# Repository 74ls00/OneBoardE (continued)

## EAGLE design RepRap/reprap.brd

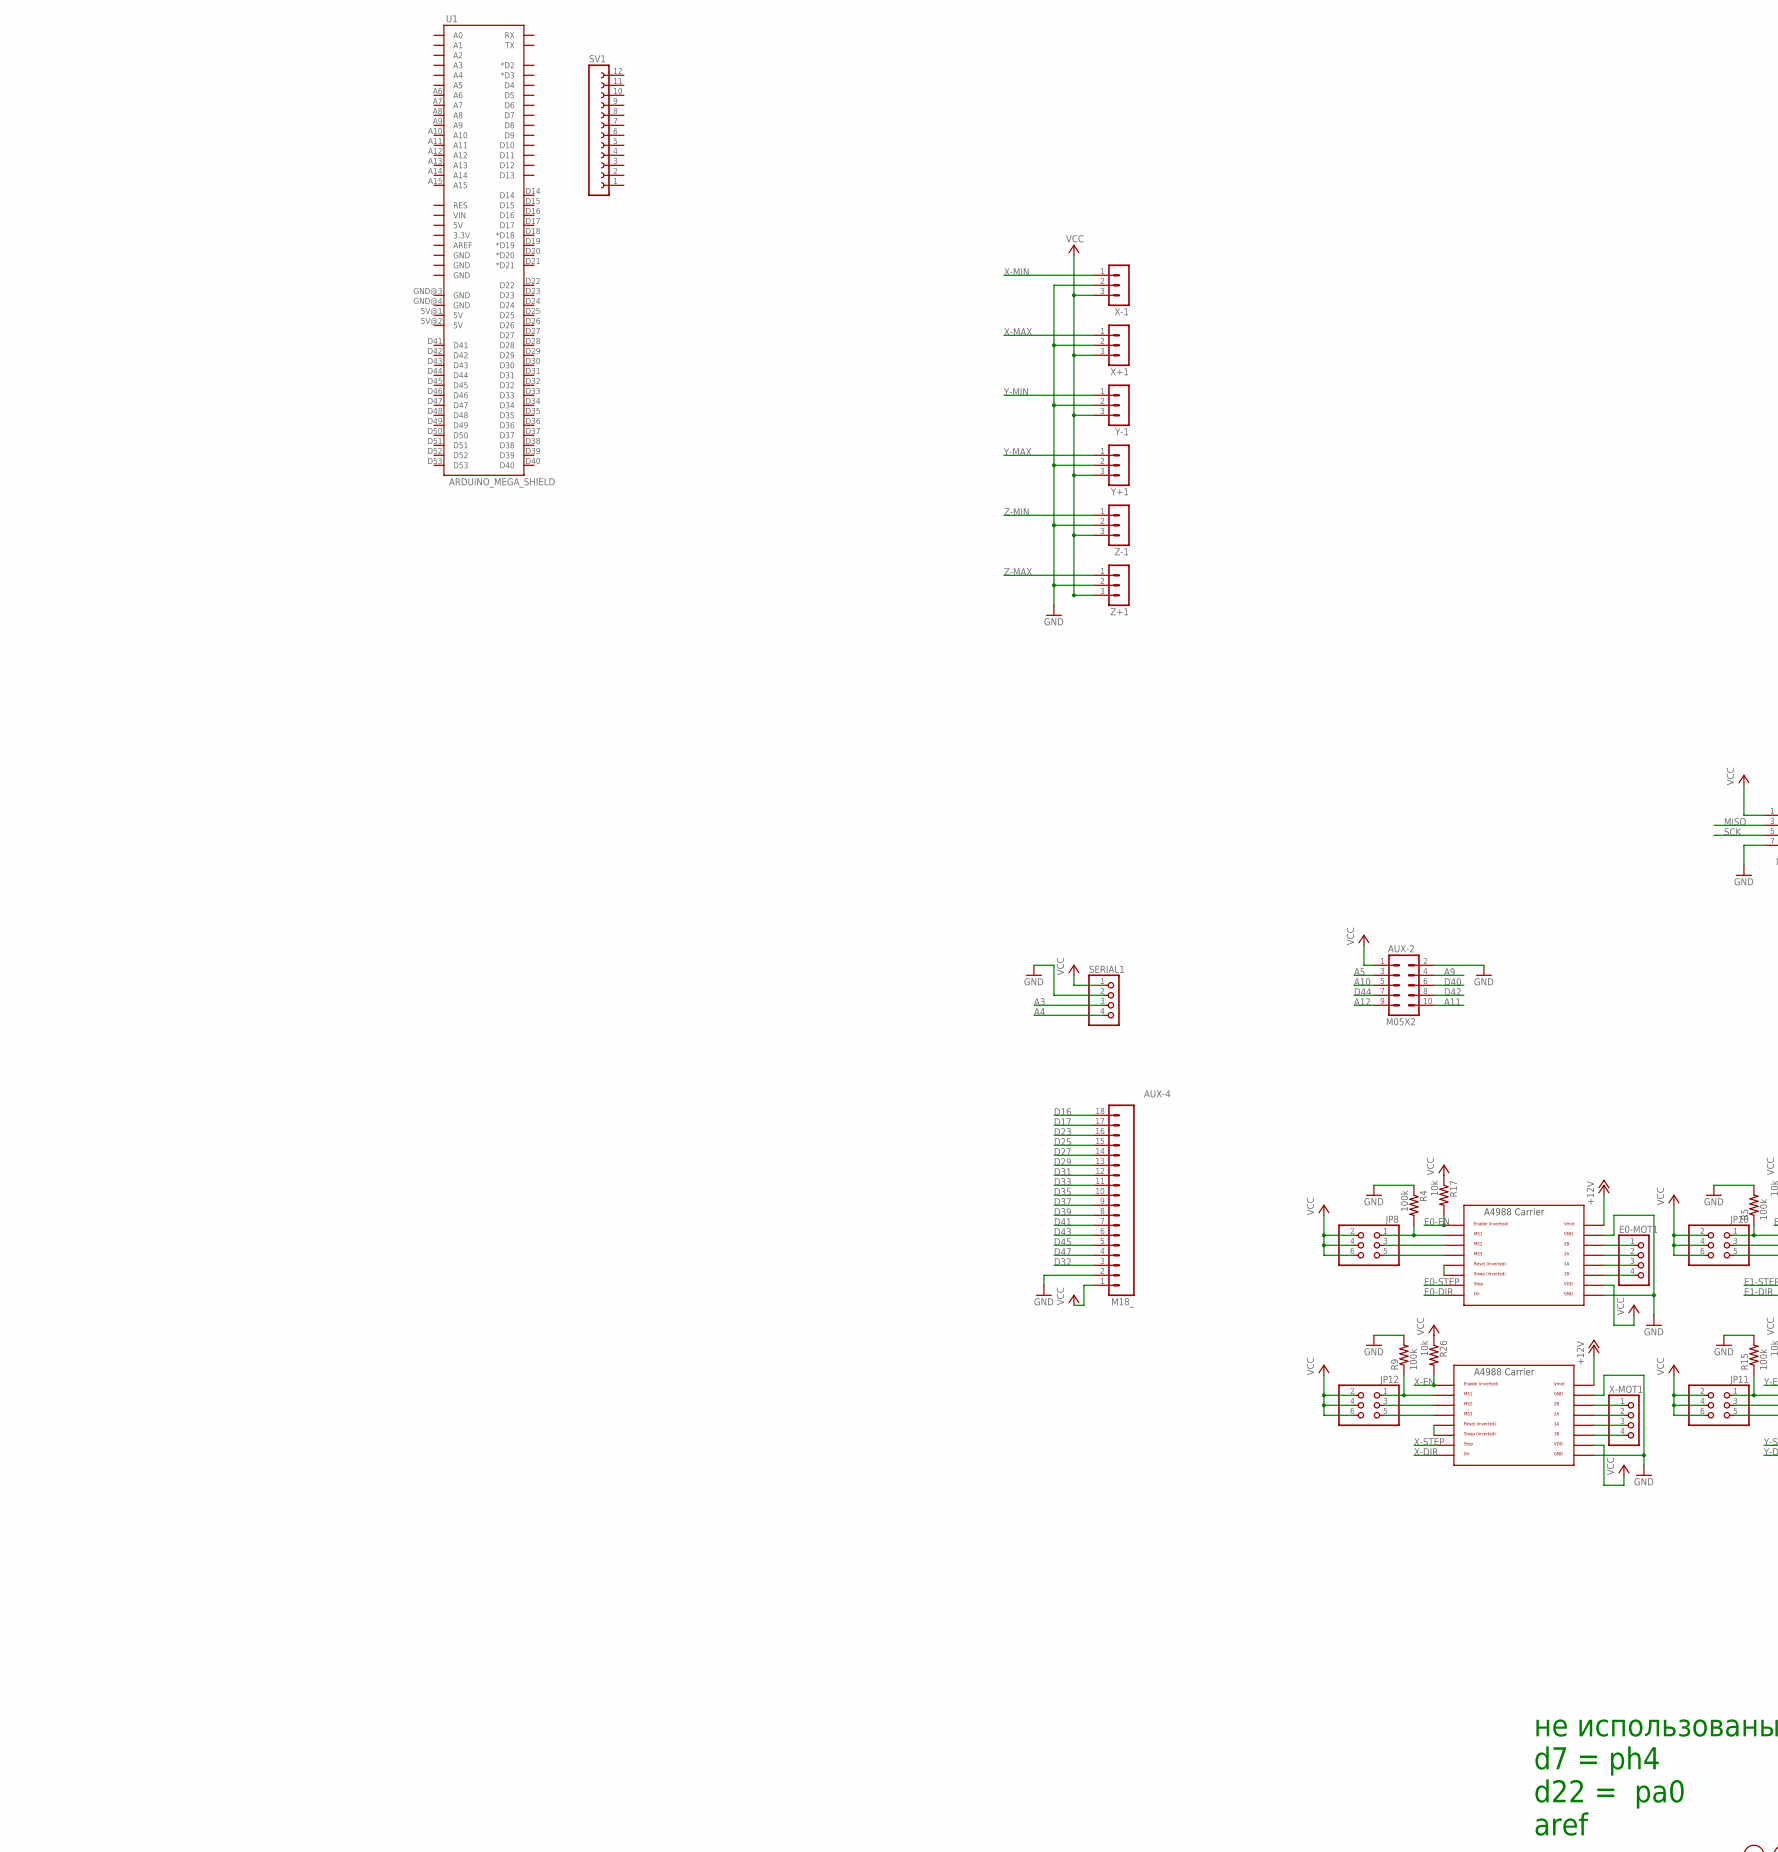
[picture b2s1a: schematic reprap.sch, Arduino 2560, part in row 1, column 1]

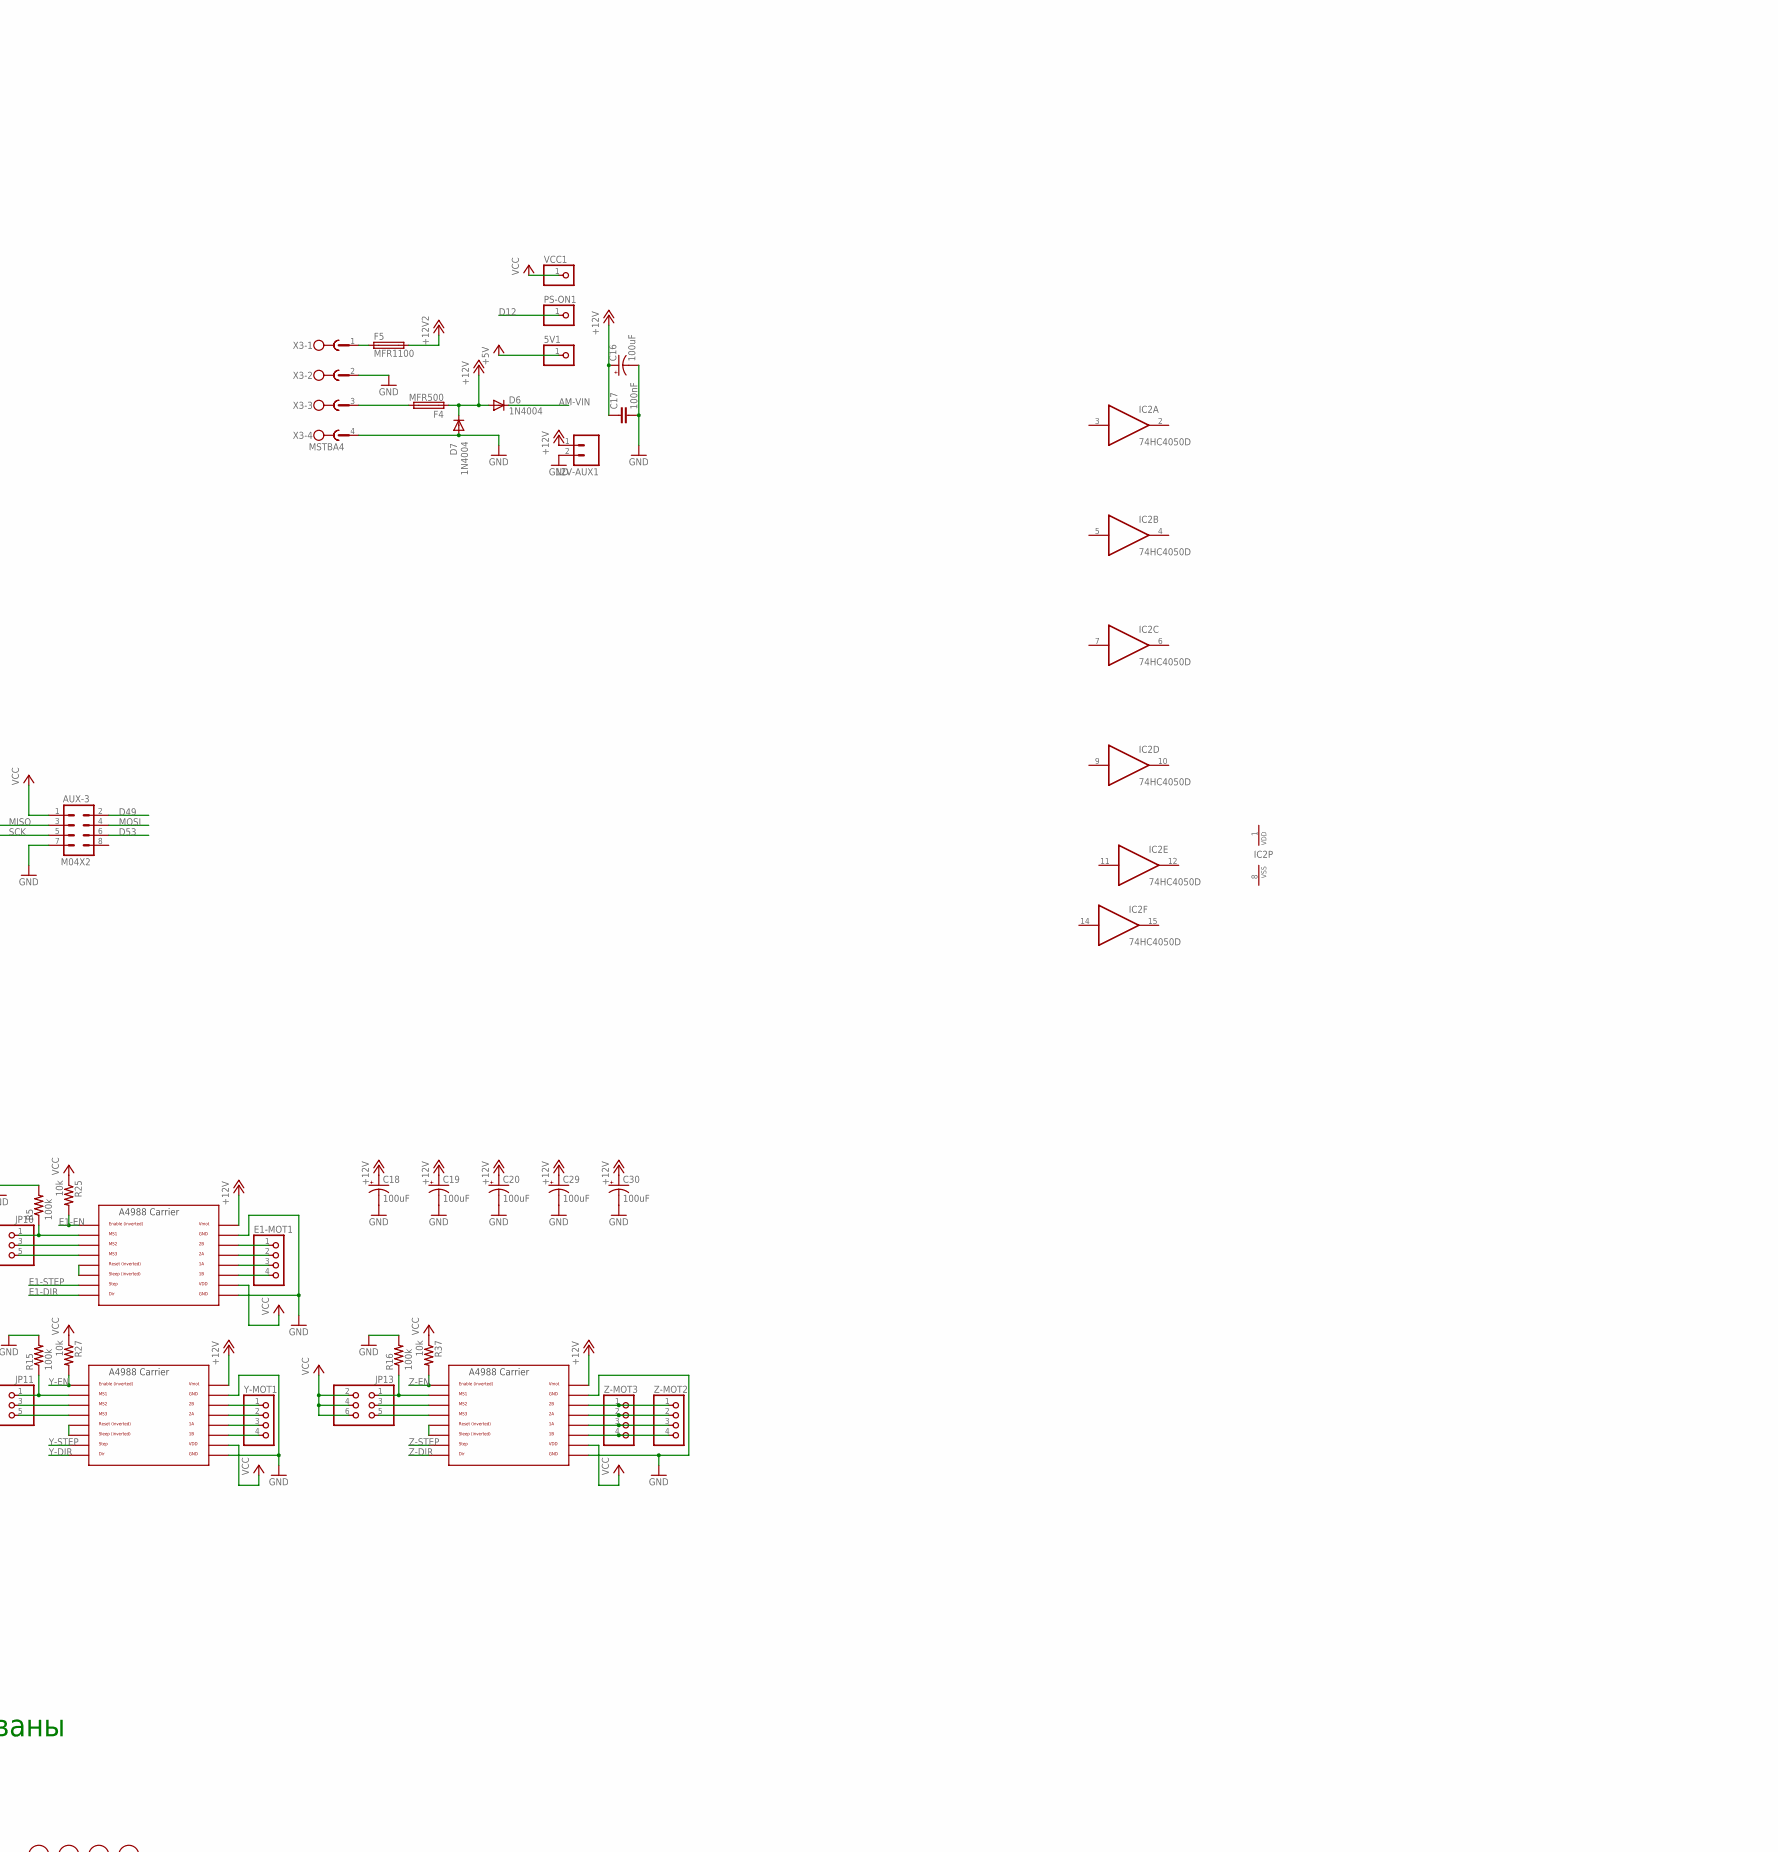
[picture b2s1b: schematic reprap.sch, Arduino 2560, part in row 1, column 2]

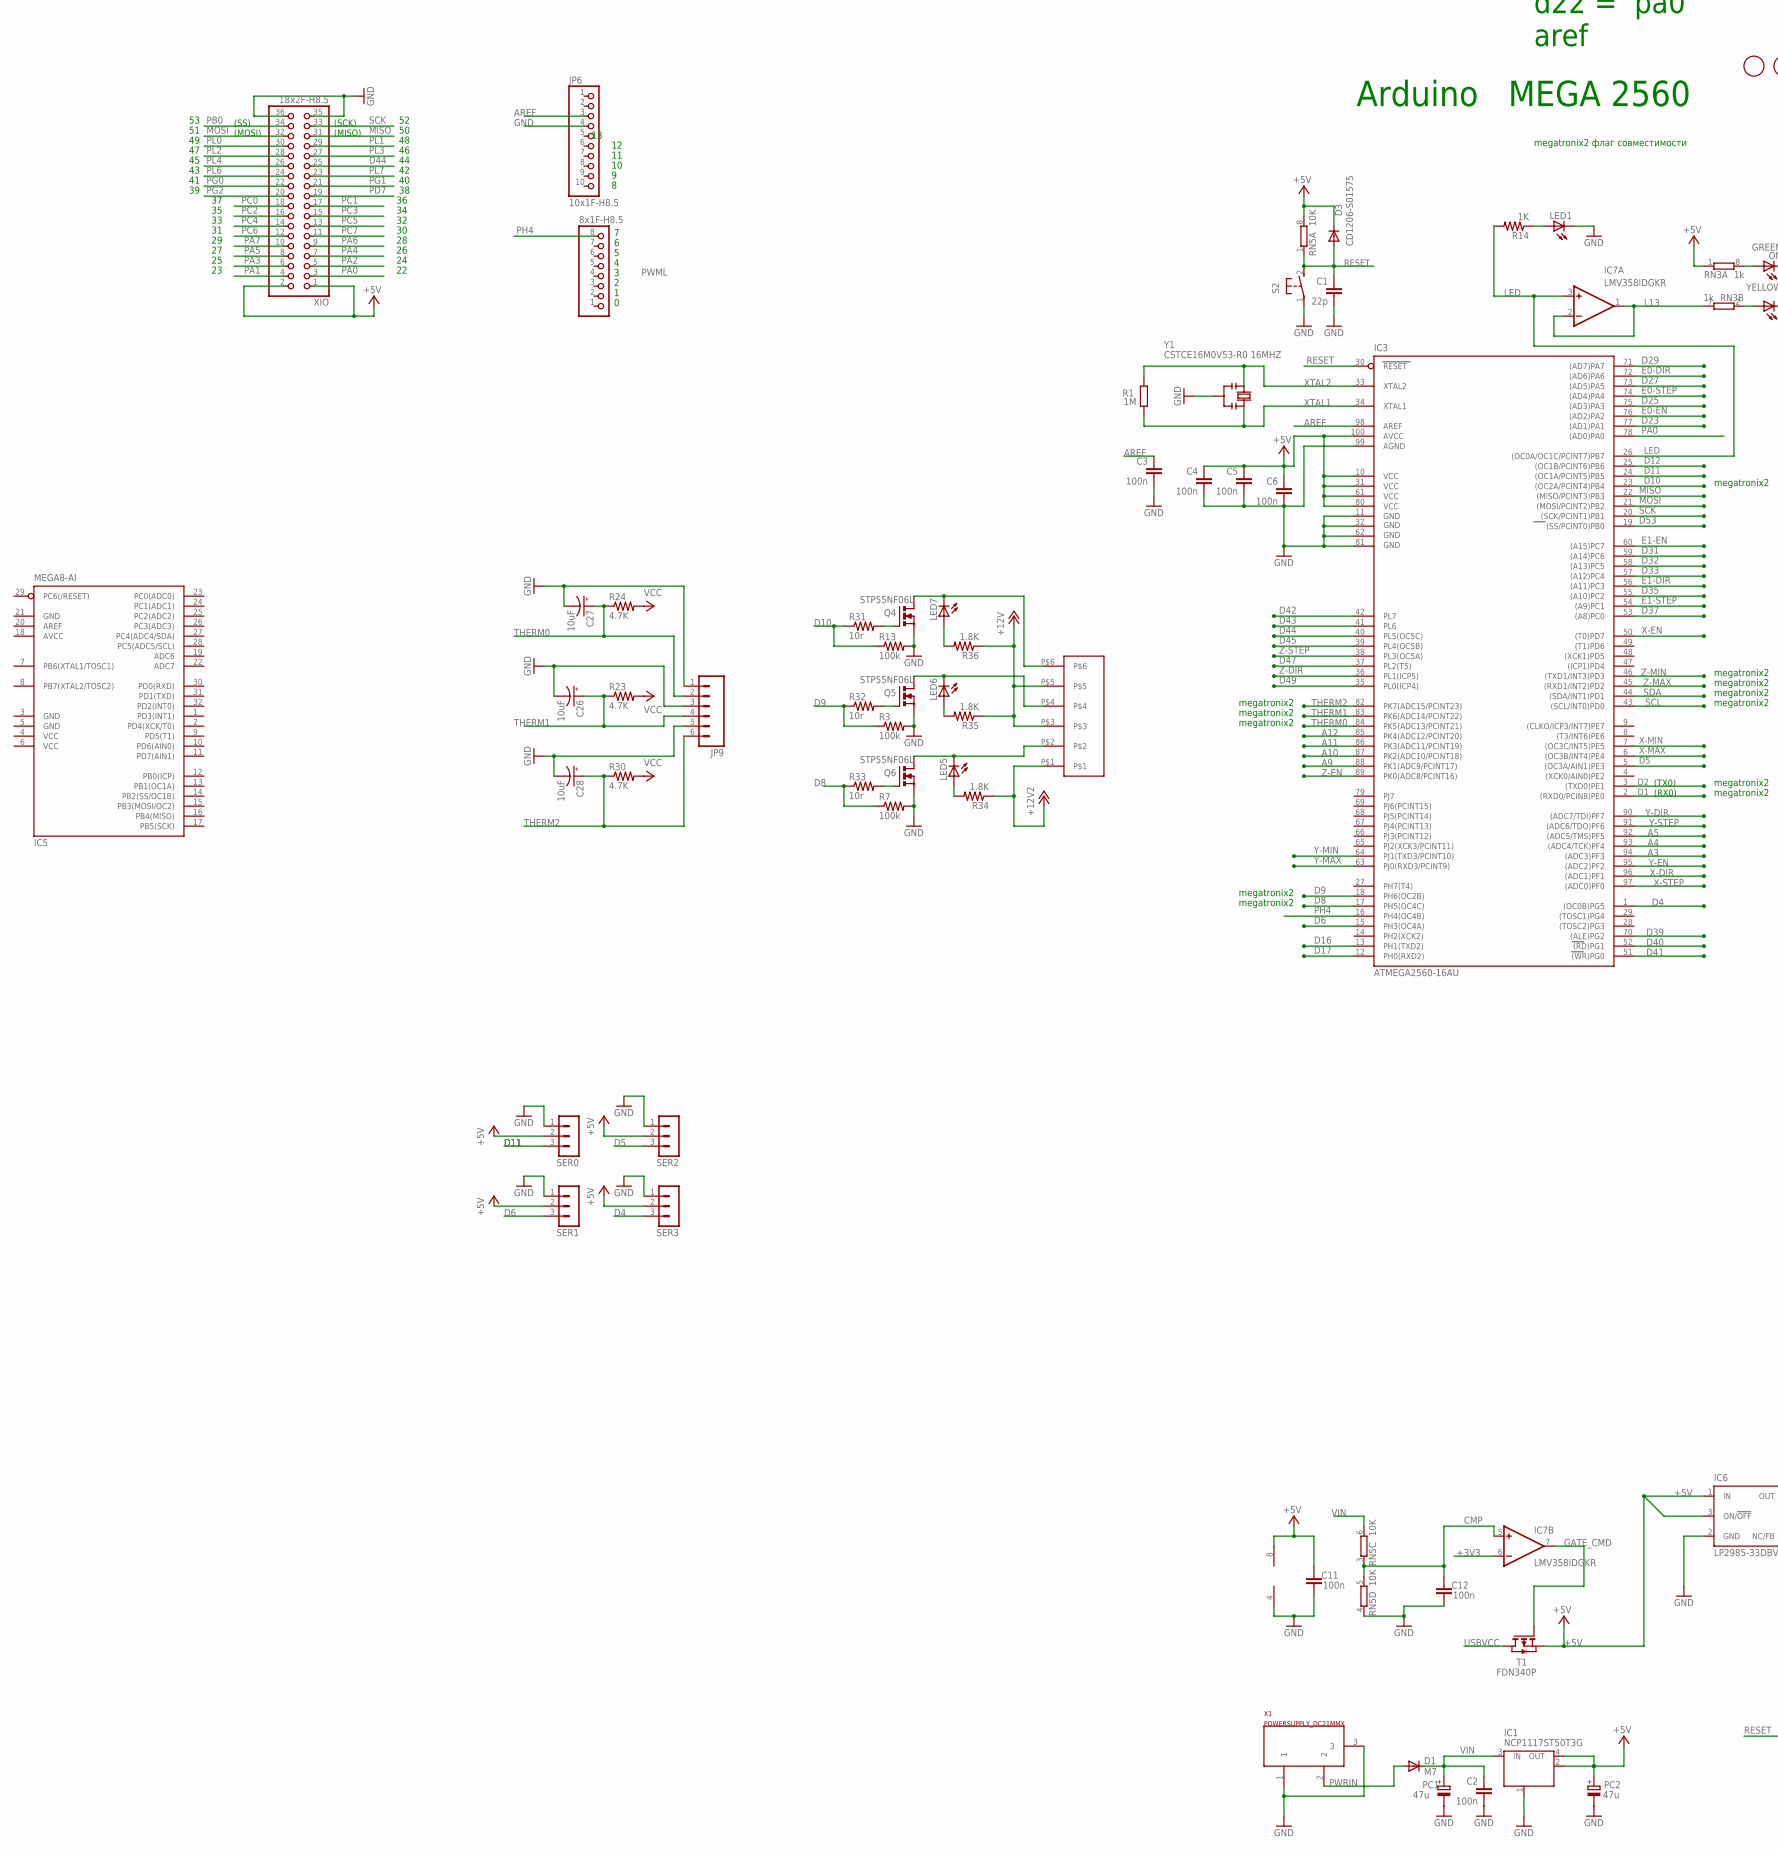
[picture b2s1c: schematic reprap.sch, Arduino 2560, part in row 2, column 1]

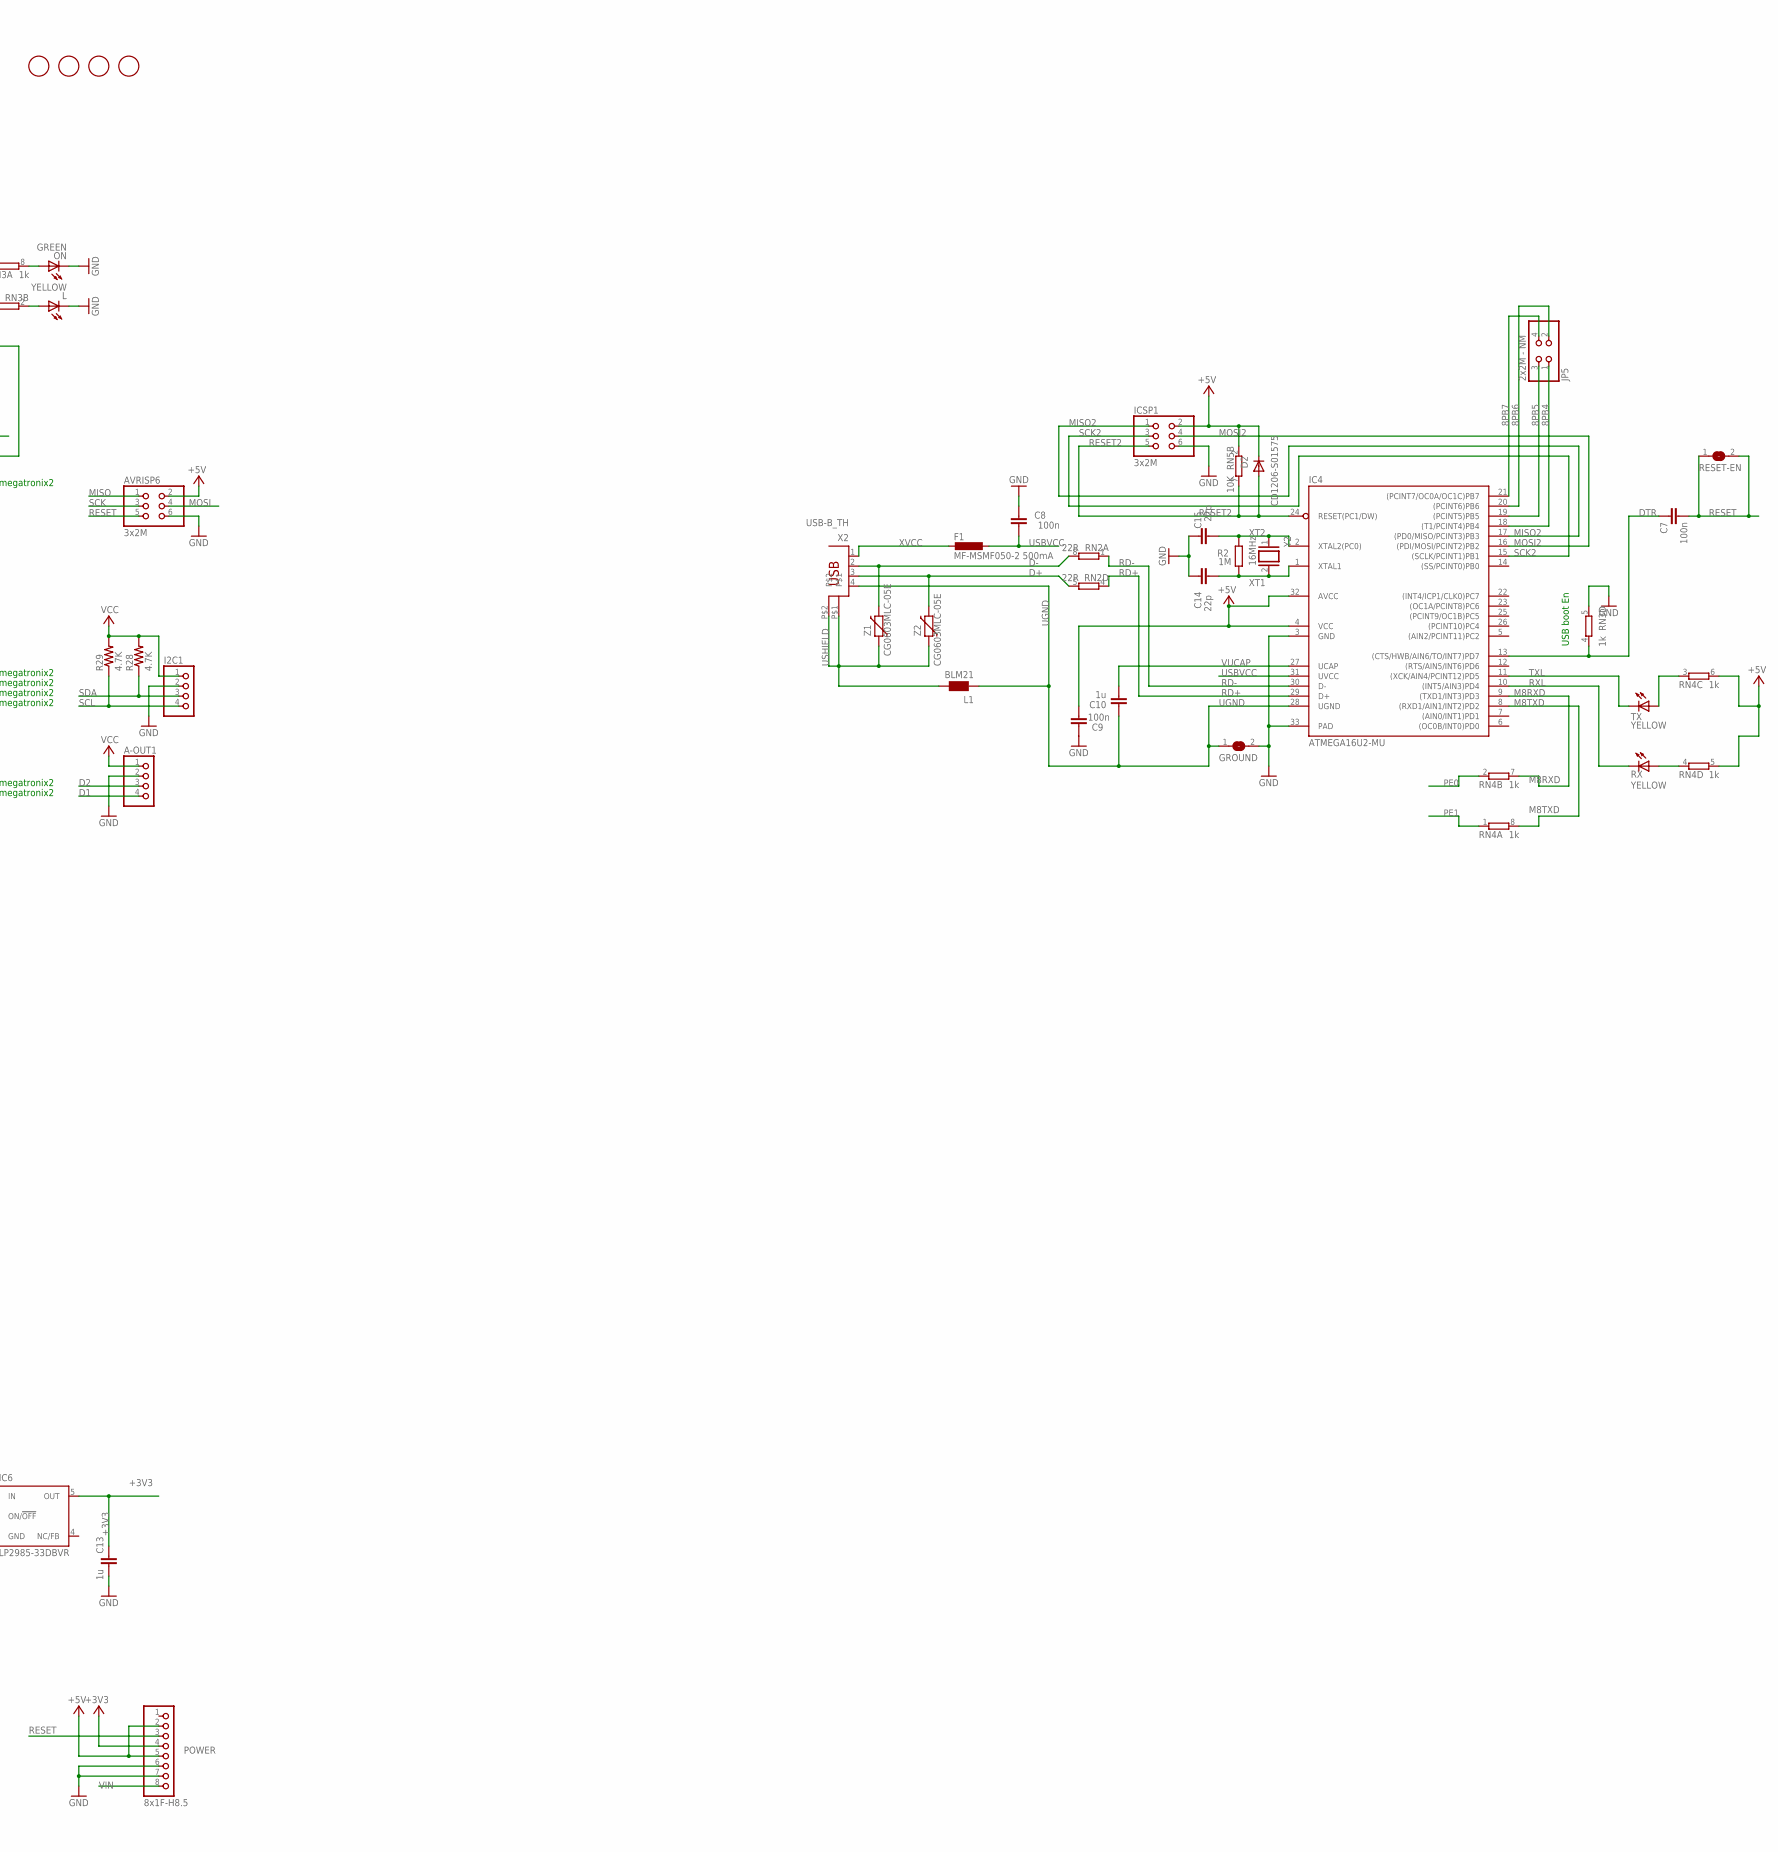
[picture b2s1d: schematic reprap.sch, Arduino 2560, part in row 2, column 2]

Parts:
5V1: PINHD-1X1; 1X01
12V-AUX1: M02PTH; 1X02
A-OUT1: PINHD-1X4; 1X04
AUX-2: M05X2; 2X5
AUX-3: M04X2; 2X4
AUX-4: M18_; 1X18
AVRISP6: 3x2M; 2X03
C1, C14, C15: 22p; C0603-ROUND
C2, C3, C4, C5, C6, C7, C8, C9, C11, C12: 100n; C0603-ROUND
C10, C13: 1u; C0603-ROUND
C16, C18, C19, C20, C29, C30: 100uF; 153CLV-0605
C17: 100nF; C0805
C26, C27, C28: 10uF; 153CLV-0405
D1: M7; SMB
D2, D3: CD1206-S01575; MINIMELF
D6, D7: 1N4004; DO41-10
E0-MOT1, E1-MOT1: PINHD-1X4; 1X04
F1: MF-MSMF050-2 500mA; L1812
F4: MFR500
F5: MFR1100
FD1, FD2, FD3, FD4: FIDUCIALMOUNT; FIDUCIA-MOUNT
GROUND: SJ
I2C1: PINHD-1X4; 1X04
IC1: NCP1117ST50T3G; SOT223
IC2: 74HC4050D; SO16
IC3: ATMEGA2560-16AU; TQFP100
IC4: ATMEGA16U2-MU; MLF32
IC5: MEGA8-AI; TQFP32-08
IC6: LP2985-33DBVR; SOT23-DBV
IC7: LMV358IDGKR; MSOP08
ICSP1: 3x2M; 2X03
JP5: 2x2M - NM; 2X02
JP6: 10x1F-H8.5; 1X10
JP8, JP10, JP11, JP12, JP13: PINHD-2X3; 2X03
JP9: M06SIP; 1X06
L: YELLOW; CHIP-LED0805
L1: BLM21; 0805
LED1, LED5, LED6, LED7: LEDCHIP-LED0805; CHIP-LED0805
ON: GREEN; CHIP-LED0805
PC1, PC2: 47u; PANASONIC_D
POWER: 8x1F-H8.5; 1X08
PS-ON1: PINHD-1X1; 1X01
PWML: 8x1F-H8.5; 1X08
Q4, Q5, Q6: STP55NF06L; TO220BV
R1, R2: 1M; R0603-ROUND
R3, R4, R5, R7, R9, R13, R15, R16: 100k; R0805
R14: 1K; R0805
R17, R25, R26, R27, R37: 10k; R0805
R23, R24, R28, R29, R30: 4.7K; R0805
R31, R33: 10r; R0805
R32: 10r; M0805
R34, R35, R36: 1.8K; R0805
RESET-EN: SJ
RN2: 22R; CAY16
RN3, RN4: 1k; CAY16
RN5: 10K; CAT16
RX: YELLOW; CHIP-LED0805
S2: 31-XX; B3F-31XX
SER0, SER1, SER2, SER3: 3PIN-HEADER
SERIAL1: PINHD-1X4; 1X04
SV1: FE12-1; FE12
T1: FDN340P; SOT-23
TX: YELLOW; CHIP-LED0805
U1: ARDUINO_MEGA_SHIELD
U$1: 282837-6
U$2, U$3, U$9, U$10, U$11: A4988BREAKOUT
VCC1: PINHD-1X1; 1X01
X1: POWERSUPPLY_DC21MMX; POWERSUPPLY_DC-21MM
X2: USB-B_TH; PN61729
X3: MSTBA4
X+1: 3PIN-HEADER
X-1: 3PIN-HEADER
X-MOT1: PINHD-1X4; 1X04
XIO: 18x2F-H8.5; 2X18
Y1: CSTCE16M0V53-R0 16MHZ; RESONATOR
Y2: 16MHz; QS
Y+1: 3PIN-HEADER
Y-1: 3PIN-HEADER
Y-MOT1: PINHD-1X4; 1X04
Z1, Z2: CG0603MLC-05E; CT/CN0603
Z+1: 3PIN-HEADER
Z-1: 3PIN-HEADER
Z-MOT2, Z-MOT3: PINHD-1X4; 1X04

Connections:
5V: U1.5V@0 (5V)
8PB4: IC4.18 ((T1/PCINT4)PB4), JP5.1
8PB5: IC4.19 ((PCINT5)PB5), JP5.3
8PB6: IC4.20 ((PCINT6)PB6), JP5.2
8PB7: IC4.21 ((PCINT7/OC0A/OC1C)PB7), JP5.4
+3V3: C13.2, IC6.5 (OUT), IC7.6 (-IN), POWER.4
+5V: 5V1.1, AVRISP6.2, C4.1, C5.1, C6.1, C9.1, C11.2, D2.C, D3.C, IC1.2 (OUT), IC1.4 (OUT), IC3.10 (VCC), IC3.31 (VCC1), IC3.61 (VCC2), IC3.80 (VCC3), IC3.100 (AVCC), IC4.4 (VCC), IC4.32 (AVCC), IC6.1 (IN), IC6.3 (ON/!OFF), IC7.8 (V+), ICSP1.2, PC2.+, POWER.2, POWER.5, RN3.1, RN4.5 (2), RN4.6 (2), RN5.2 (1), RN5.8 (2), SER0.2, SER1.2, SER2.2, SER3.2, T1.2 (S), XIO.1, XIO.2
+12V: 12V-AUX1.1, C16.+, C17.1, C18.+, C19.+, C20.+, C29.+, C30.+, D6.A, D7.C, F4.1, R35.1, R36.1, U$1.P$3, U$1.P$5, U$2.VMOT, U$3.VMOT, U$9.VMOT, U$10.VMOT, U$11.VMOT
+12V2: F5.2, R34.1, U$1.P$1
A3: IC3.94 ((ADC3)PF3), SERIAL1.3
A4: IC3.93 ((ADC4/TCK)PF4), SERIAL1.4
A5: AUX-2.3, IC3.92 ((ADC5/TMS)PF5)
A9: AUX-2.4, IC3.88 (PK1(ADC9/PCINT17))
A10: AUX-2.5, IC3.87 (PK2(ADC10/PCINT18))
A11: AUX-2.10, IC3.86 (PK3(ADC11/PCINT19))
A12: AUX-2.9, IC3.85 (PK4(ADC12/PCINT20))
AM-VIN: D6.C
AREF: C3.1, IC3.98 (AREF), JP6.3
AVCC: IC5.18 (AVCC)
CMP: C12.2, IC7.5 (+IN), RN5.3 (1), RN5.5 (2)
D1: A-OUT1.4, IC3.2 ((RXD0/PCIN8)PE0)
D2: A-OUT1.3, IC3.3 ((TXD0)PE1)
D4: IC3.1 ((OC0B)PG5), SER3.3
D5: IC3.5 ((OC3A/AIN1)PE3), SER2.3
D6: IC3.15 (PH3(OC4A)), SER1.3
D8: IC3.17 (PH5(OC4C)), R7.1, R33.1
D9: IC3.18 (PH6(OC2B)), R3.1, R32.1
D10: IC3.23 ((OC2A/PCINT4)PB4), R13.1, R31.1
D11: IC3.24 ((OC1A/PCINT5)PB5), SER0.3
D12: IC3.25 ((OC1B/PCINT6)PB6), PS-ON1.1
D16: AUX-4.18, IC3.13 (PH1(TXD2))
D17: AUX-4.17, IC3.12 (PH0(RXD2))
D23: AUX-4.16, IC3.77 ((AD1)PA1)
D25: AUX-4.15, IC3.75 ((AD3)PA3)
D27: AUX-4.14, IC3.73 ((AD5)PA5)
D29: AUX-4.13, IC3.71 ((AD7)PA7)
D31: AUX-4.12, IC3.59 ((A14)PC6)
D32: AUX-4.3, IC3.58 ((A13)PC5)
D33: AUX-4.11, IC3.57 ((A12)PC4)
D35: AUX-4.10, IC3.55 ((A10)PC2)
D37: AUX-4.9, IC3.53 ((A8)PC0)
D39: AUX-4.8, IC3.70 ((ALE)PG2)
D40: AUX-2.6, IC3.52 ((RD)PG1)
D41: AUX-4.7, IC3.51 ((WR)PG0)
D42: AUX-2.8, IC3.42 (PL7)
D43: AUX-4.6, IC3.41 (PL6)
D44: AUX-2.7, IC3.40 (PL5(OC5C)), XIO.25
D45: AUX-4.5, IC3.39 (PL4(OC5B))
D47: AUX-4.4, IC3.37 (PL2(T5))
D49: AUX-3.2, IC3.35 (PL0(ICP4))
D53: AUX-3.6, IC3.19 ((SS/PCINT0)PB0)
D+: RN2.5 (2), X2.3, Z2.2
D-: RN2.8 (2), X2.2, Z1.2
DTR: C7.1, IC4.13 ((CTS/HWB/AIN6/TO/INT7)PD7), RN3.4 (1)
E0-DIR: IC3.72 ((AD6)PA6), U$2.DIR
E0-EN: IC3.76 ((AD2)PA2), R17.2, U$2.EN
E0-STEP: IC3.74 ((AD4)PA4), U$2.STEP
E1-DIR: IC3.56 ((A11)PC3), U$3.DIR
E1-EN: IC3.60 ((A15)PC7), R25.2, U$3.EN
E1-STEP: IC3.54 ((A9)PC1), U$3.STEP
GATE_CMD: IC7.7 (OUT), T1.3 (G)
GND: 12V-AUX1.2, A-OUT1.2, AUX-2.2, AUX-3.7, AUX-4.2, AVRISP6.6, C1.2, C2.2, C3.2, C4.2, C5.2, C6.2, C8.2, C9.2, C11.1, C12.1, C13.1, C14.2, C15.2, C16.-, C17.2, C18.-, C19.-, C20.-, C26.-, C27.-, C28.-, C29.-, C30.-, D7.A, GROUND.2, I2C1.2, IC1.1 (GND/ADJ), IC3.11 (GND), IC3.32 (GND1), IC3.62 (GND2), IC3.81 (GND3), IC3.99 (AGND), IC4.3 (GND), IC4.33 (PAD), IC5.3 (GND), IC5.5 (GND), IC5.21 (GND), IC6.2 (GND), IC7.4 (V-), ICSP1.6, JP6.4, JP9.1, JP9.3, JP9.5, L.C, LED1.C, ON.C, PC1.-, PC2.-, POWER.6, POWER.7, Q4.S, Q5.S, Q6.S, R3.2, R4.1, R5.2, R7.2, R9.2, R13.2, R15.2, R16.2, RN3.5 (2), RN5.4 (1), S2.1, SER0.1, SER1.1, SER2.1, SER3.1, SERIAL1.2, U$2.GND, U$2.GND@0 (GND), U$3.GND, U$3.GND@0 (GND), U$9.GND, U$9.GND@0 (GND), U$10.GND, U$10.GND@0 (GND), U$11.GND, U$11.GND@0 (GND), X1.1, X1.3, X3.2, X3.4, X+1.2, X-1.2, XIO.35, XIO.36, Y1.2, Y+1.2, Y-1.2, Z+1.2, Z-1.2
L13: IC7.1 (OUT), IC7.2 (-IN), RN3.7 (2)
LED: IC3.26 ((OC0A/OC1C/PCINT7)PB7), IC7.3 (+IN), R14.2
M8RXD: IC4.9 ((TXD1/INT3)PD3), RN4.7 (2)
M8TXD: IC4.8 ((RXD1/AIN1/INT2)PD2), RN4.8 (2)
MISO: AUX-3.3, AVRISP6.1, IC3.22 ((MISO/PCINT3)PB3), XIO.31
MISO2: IC4.17 ((PD0/MISO/PCINT3)PB3), ICSP1.1
MOSI: AUX-3.4, AVRISP6.4, IC3.21 ((MOSI/PCINT2)PB2), XIO.32
MOSI2: IC4.16 ((PDI/MOSI/PCINT2)PB2), ICSP1.4
unnamed: F5.1, X3.1
unnamed: L.A, RN3.2 (1)
unnamed: ON.A, RN3.8 (2)
unnamed: F4.2, X3.3
unnamed: LED6.C, Q5.D, U$1.P$4
unnamed: JP8.5, U$2.MS3
unnamed: U$2.RST, U$2.SLP (SLEEP)
unnamed: JP12.5, U$9.MS3
unnamed: U$9.RST, U$9.SLP (SLEEP)
unnamed: JP11.3, U$10.MS2
unnamed: RN4.4 (1), RX.A
unnamed: RN4.3 (1), TX.A
unnamed: U$10.RST, U$10.SLP (SLEEP)
unnamed: LED1.A, R14.1
unnamed: LED5.C, Q6.D, U$1.P$2
unnamed: LED7.C, Q4.D, U$1.P$6
unnamed: Q5.G, R32.2
unnamed: Q4.G, R31.2
unnamed: Q6.G, R33.2
unnamed: LED5.A, R34.2
unnamed: LED6.A, R35.2
unnamed: LED7.A, R36.2
unnamed: U$3.RST, U$3.SLP (SLEEP)
unnamed: JP10.1, R5.1, U$3.MS1
unnamed: JP8.1, R4.2, U$2.MS1
unnamed: JP8.3, U$2.MS2
unnamed: JP12.1, R9.1, U$9.MS1
unnamed: JP12.3, U$9.MS2
unnamed: JP11.5, U$10.MS3
unnamed: JP11.1, R15.1, U$10.MS1
unnamed: JP10.5, U$3.MS3
unnamed: JP10.3, U$3.MS2
unnamed: E0-MOT1.1, U$2.2B
unnamed: E0-MOT1.2, U$2.2A
unnamed: E0-MOT1.3, U$2.1A
unnamed: E0-MOT1.4, U$2.1B
unnamed: E1-MOT1.1, U$3.2B
unnamed: E1-MOT1.2, U$3.2A
unnamed: E1-MOT1.3, U$3.1A
unnamed: E1-MOT1.4, U$3.1B
unnamed: U$9.2B, X-MOT1.1
unnamed: U$9.2A, X-MOT1.2
unnamed: U$9.1A, X-MOT1.3
unnamed: U$9.1B, X-MOT1.4
unnamed: U$10.2B, Y-MOT1.1
unnamed: U$10.2A, Y-MOT1.2
unnamed: U$10.1A, Y-MOT1.3
unnamed: U$10.1B, Y-MOT1.4
unnamed: JP13.3, U$11.MS2
unnamed: U$11.RST, U$11.SLP (SLEEP)
unnamed: JP13.5, U$11.MS3
unnamed: JP13.1, R16.1, U$11.MS1
unnamed: U$11.2B, Z-MOT2.1, Z-MOT3.1
unnamed: U$11.2A, Z-MOT2.2, Z-MOT3.2
unnamed: U$11.1A, Z-MOT2.3, Z-MOT3.3
unnamed: U$11.1B, Z-MOT2.4, Z-MOT3.4
PA0: IC3.78 ((AD0)PA0), XIO.3
PA1: XIO.4
PA2: XIO.5
PA3: XIO.6
PA4: XIO.7
PA5: XIO.8
PA6: XIO.9
PA7: XIO.10
PB0: XIO.34
PC0: XIO.18
PC1: XIO.17
PC2: XIO.16
PC3: XIO.15
PC4: XIO.14
PC5: XIO.13
PC6: XIO.12
PC7: XIO.11
PD7: XIO.19
PE0: RN4.2 (1)
PE1: RN4.1
PG0: XIO.22
PG1: XIO.21
PG2: XIO.20
PH4: IC3.16 (PH4(OC4B)), PWML.8
PL0: XIO.30
PL1: XIO.29
PL2: XIO.28
PL3: XIO.27
PL4: XIO.26
PL6: XIO.24
PL7: XIO.23
PWRIN: D1.A, X1.2
RD+: IC4.29 (D+), RN2.4 (1)
RD-: IC4.30 (D-), RN2.1
RESET: AVRISP6.5, C1.1, C7.2, D3.A, IC3.30 (RESET), POWER.3, RESET-EN.1, RESET-EN.2, RN5.1, S2.2 (S)
RESET2: D2.A, IC4.24 (RESET(PC1/DW)), ICSP1.5, RN5.7 (2)
RXL: IC4.10 ((INT5/AIN3)PD4), RX.C
SCK: AUX-3.5, AVRISP6.3, IC3.20 ((SCK/PCINT1)PB1), XIO.33
SCK2: IC4.15 ((SCLK/PCINT1)PB1), ICSP1.3
SCL: I2C1.4, IC3.43 ((SCL/INT0)PD0), R29.1
SDA: I2C1.3, IC3.44 ((SDA/INT1)PD1), R28.1
THERM0: C27.+, IC3.84 (PK5(ADC13/PCINT21)), JP9.2, R24.1
THERM1: C26.+, IC3.83 (PK6(ADC14/PCINT22)), JP9.4, R23.1
THERM2: C28.+, IC3.82 (PK7(ADC15/PCINT23)), JP9.6, R30.1
TXL: IC4.11 ((XCK/AIN4/PCINT12)PD5), TX.C
UGND: C10.2, GROUND.1, IC4.28 (UGND), L1.1, X2.4
USBVCC: C8.1, F1.1, IC4.31 (UVCC), T1.1 (D)
USHIELD: L1.2, X2.P$1, X2.P$2, Z1.1, Z2.1
VCC: A-OUT1.1, AUX-2.1, AUX-3.1, AUX-4.1, I2C1.1, IC5.4 (VCC), IC5.6 (VCC), JP8.2, JP8.4, JP8.6, JP10.2, JP10.4, JP10.6, JP11.2, JP11.4, JP11.6, JP12.2, JP12.4, JP12.6, JP13.2, JP13.4, JP13.6, R17.1, R23.2, R24.2, R25.1, R26.1, R27.1, R28.2, R29.2, R30.2, R37.1, SERIAL1.1, U$2.VDD, U$3.VDD, U$9.VDD, U$10.VDD, U$11.VDD, VCC1.1, X+1.3, X-1.3, Y+1.3, Y-1.3, Z+1.3, Z-1.3
VDD: IC2.1 (VDD)
VIN: C2.1, D1.C, IC1.3 (IN), PC1.+, POWER.8, RN5.6 (2)
VSS: IC2.8 (VSS)
VUCAP: C10.1, IC4.27 (UCAP)
X-DIR: IC3.96 ((ADC1)PF1), U$9.DIR
X-EN: IC3.50 ((T0)PD7), R26.2, U$9.EN
X-MAX: IC3.6 ((OC3B/INT4)PE4), X+1.1
X-MIN: IC3.7 ((OC3C/INT5)PE5), X-1.1
X-STEP: IC3.97 ((ADC0)PF0), U$9.STEP
XT1: C14.1, IC4.1 (XTAL1), R2.1, Y2.2
XT2: C15.1, IC4.2 (XTAL2(PC0)), R2.2, Y2.1
XTAL1: IC3.34 (XTAL1), R1.1, Y1.3
XTAL2: IC3.33 (XTAL2), R1.2, Y1.1
XVCC: F1.2, X2.1
Y-DIR: IC3.90 ((ADC7/TDI)PF7), U$10.DIR
Y-EN: IC3.95 ((ADC2)PF2), R27.2, U$10.EN
Y-MAX: IC3.63 (PJ0(RXD3/PCINT9)), Y+1.1
Y-MIN: IC3.64 (PJ1(TXD3/PCINT10)), Y-1.1
Y-STEP: IC3.91 ((ADC6/TDO)PF6), U$10.STEP
Z-DIR: IC3.36 (PL1(ICP5)), U$11.DIR
Z-EN: IC3.89 (PK0(ADC8/PCINT16)), R37.2, U$11.EN
Z-MAX: IC3.45 ((RXD1/INT2)PD2), Z+1.1
Z-MIN: IC3.46 ((TXD1/INT3)PD3), Z-1.1
Z-STEP: IC3.38 (PL3(OC5A)), U$11.STEP

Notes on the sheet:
Arduino MEGA 2560
(TX0)
(RX0)
(SS)
(MOSI)
(SCK)
(MISO)
USB boot En
не использованы d7 = ph4 d22 = pa0 aref
megatronix2
megatronix2 флаг совместимости

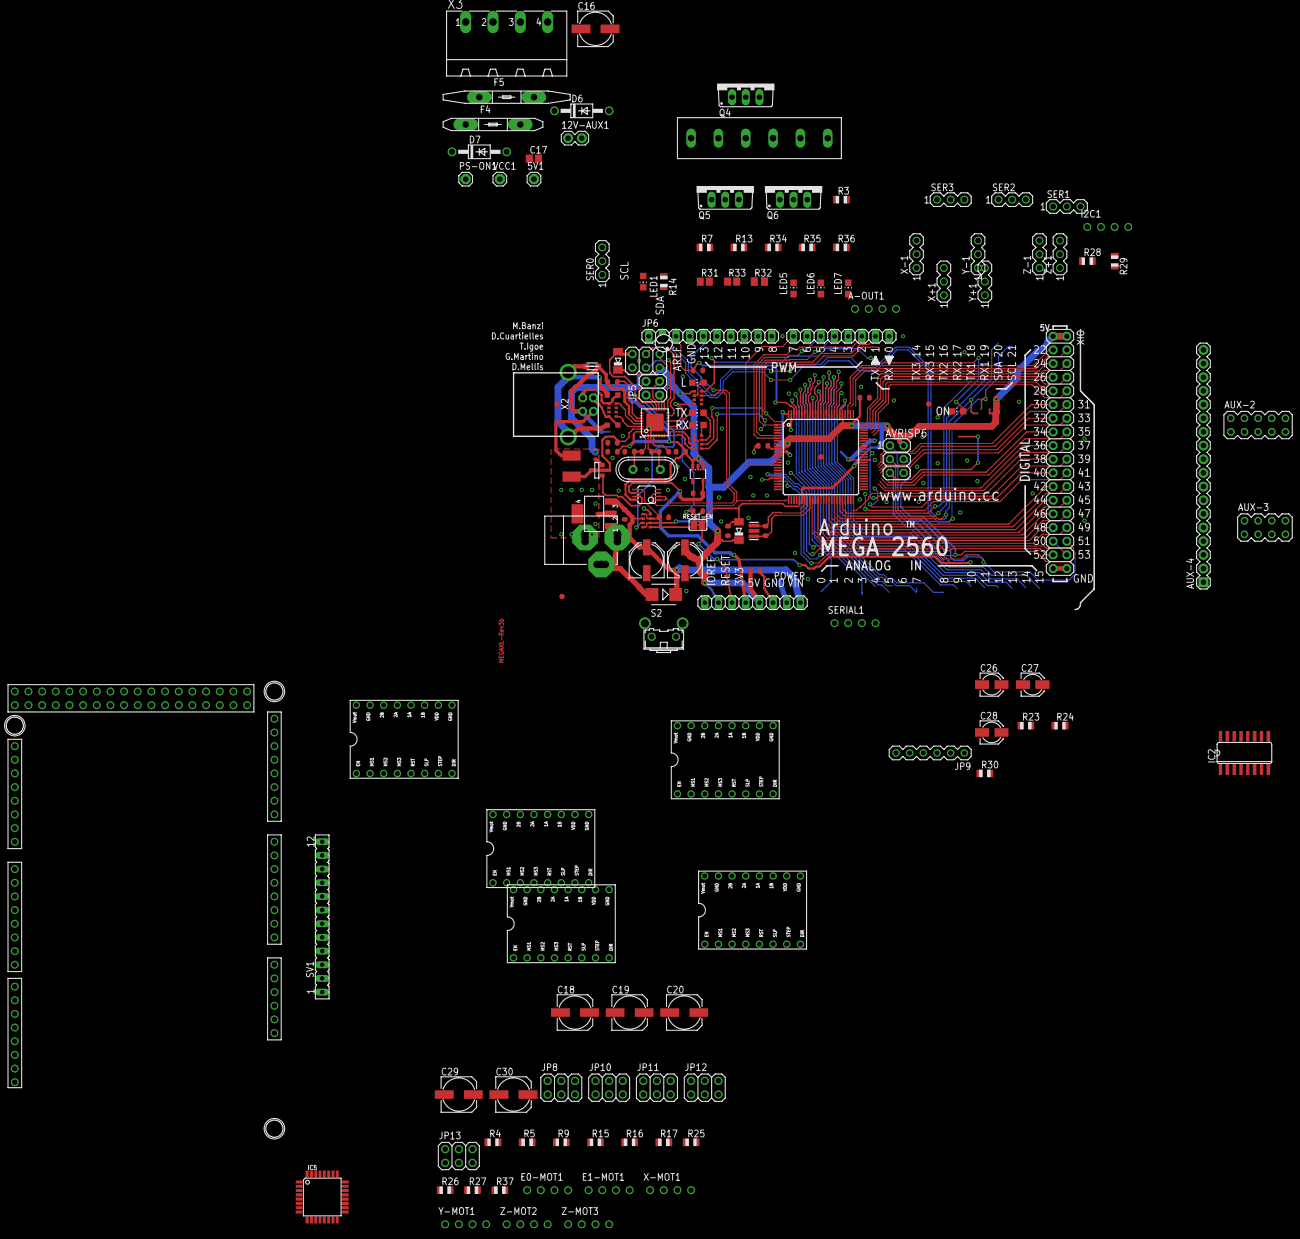
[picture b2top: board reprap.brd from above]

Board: 2 copper layers, 147 parts (1 on the bottom side), 165 nets.

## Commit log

2016-05-17 0001
2016-05-18 add libs
2016-05-22 160522
